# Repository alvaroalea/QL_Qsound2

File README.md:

# Sinclair QL Qsound2+
## Soundcard compatible with QsoundQprint for Sinclair QL

WARNING!!!  Actually there is a problem with this design and is not Fully Compatible with QSound, still need to do more test, music sound at half frecuency, so it's out of tune, and probably effects will be diferents.

(C) 2024 Alvaro Alea Fernandez

License under: CERN Open Hardware Licence Version 2 - Strongly Reciprocal

https://ohwr.org/cern_ohl_s_v2.txt

I upgrade the original desing:

- Using a YM2203, compatible with AY-3-8910 but add a FM sound Chanel
- Add a second way to access the chip, without the PIA (MC6821) to speedup the access.
- Fixed 2Mhz clock, same that Atari ST
- Stereo Output (ABC or ACB selectable by jumpers)

- Remain compatible with Qsound (include a jumper to select internal clock reference as in Qsound)

You can use a 2764 eprom or a W27C512 flash, that is much more cheap and easy to use.

Refer to the original repository for more information about Qsound: https://github.com/alvaroalea/QL_QsoundQprint_clone

## Technical details:
The Card reserve 16Kb of Memory space following Sinclair's P'N'P Way, this mean that is not compatible with 768Kb Trump Card, and that in most of the QL will end on the 0xC0000 - 0xC3FFFF.

The first 8Kb are occuped by the ROM

The next  4Kb are occuped by the MC6821 like in normal QSound

The last 4Kb are used for direct access to the YM2203, it use also A1, so there are two directions:

Write 0xC3000 ->  Write Address Register

Read  0xC3000 -> Read Status

Write 0xC3002 -> Write Register Value

Read  0xC3002 -> Read Register Value

There is no way to know which Clock is selected or Stereo type, this is handmade selections.

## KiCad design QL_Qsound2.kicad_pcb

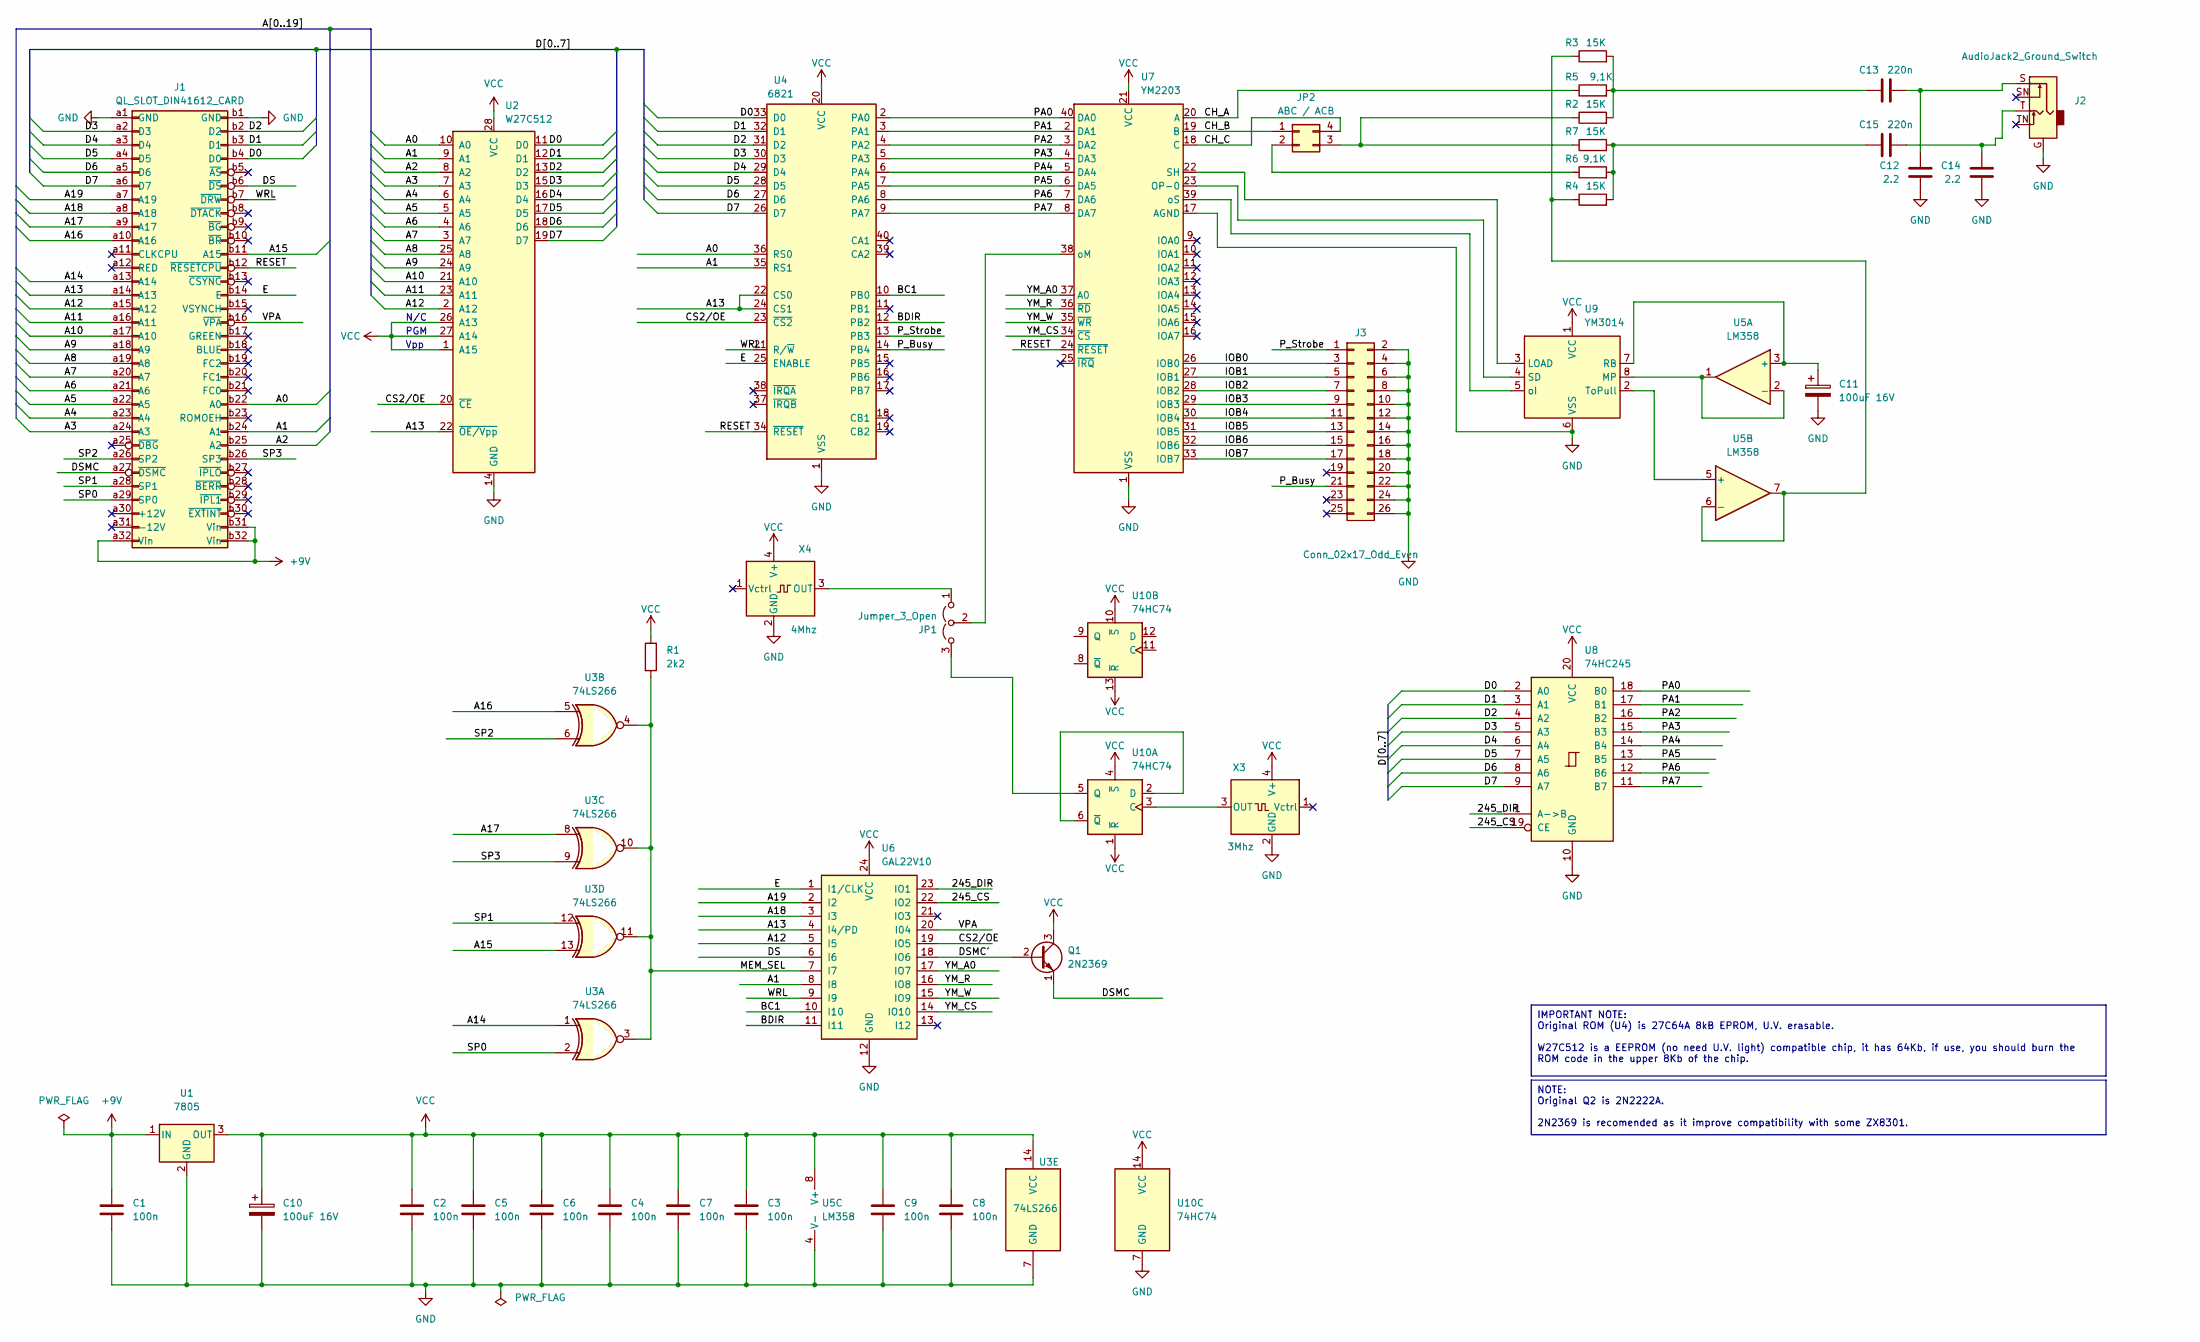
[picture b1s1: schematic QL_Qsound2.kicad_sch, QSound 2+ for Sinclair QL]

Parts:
C1, C2, C3, C4, C5, C6, C7, C8, C9: 100n; C_Disc_D4.3mm_W1.9mm_P5.00mm
C10, C11: 100uF 16V; CP_Radial_D8.0mm_P5.00mm
C12, C14: 2.2; C_Disc_D4.3mm_W1.9mm_P5.00mm
C13, C15: 220n; C_Disc_D4.3mm_W1.9mm_P5.00mm
J1: QL_SLOT_DIN41612_CARD; DIN41612_B_2x32_Female_Horizontal_THT
J2: AudioJack2_Ground_Switch
J3: Conn_02x17_Odd_Even; PinHeader_2x13_P2.54mm_Vertical
JP1: Jumper_3_Open; PinHeader_1x03_P2.54mm_Vertical
JP2: ABC / ACB; PinHeader_2x02_P2.54mm_Vertical
Q1: 2N2369; TO-92_Inline
R1: 2k2; R_Axial_DIN0207_L6.3mm_D2.5mm_P7.62mm_Horizontal
R2, R3, R4, R7: 15K; R_Axial_DIN0207_L6.3mm_D2.5mm_P7.62mm_Horizontal
R5, R6: 9,1K; R_Axial_DIN0207_L6.3mm_D2.5mm_P7.62mm_Horizontal
U1: 7805; TO-220-3_Horizontal_TabDown
U2: W27C512; DIP-28_W15.24mm_LongPads
U3: 74LS266; DIP-14_W7.62mm_LongPads
U4: 6821; DIP-40_W15.24mm_LongPads
U5: LM358; DIP-8_W7.62mm_LongPads
U6: GAL22V10; DIP-24_W7.62mm_LongPads
U7: YM2203; DIP-40_W15.24mm_LongPads
U8: 74HC245; DIP-20_W7.62mm_LongPads
U9: YM3014; DIP-8_W7.62mm_LongPads
U10: 74HC74; DIP-14_W7.62mm_LongPads
X3: 3Mhz; Oscillator_SMD_Abracon_ASV-4Pin_7.0x5.1mm
X4: 4Mhz; Oscillator_SMD_Abracon_ASV-4Pin_7.0x5.1mm

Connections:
+9V: C1.1, J1.a32 (Vin), J1.b31 (Vin), J1.b32 (Vin), U1.1 (IN)
/245_CS: U6.22 (IO2), U8.19 (CE)
/245_DIR: U6.23 (IO1), U8.1 (A->B)
/A0: J1.b22 (A0), U2.10 (A0), U4.36 (RS0)
/A1: J1.b24 (A1), U2.9 (A1), U4.35 (RS1), U6.8 (I8)
/A2: J1.b25 (A2), U2.8 (A2)
/A3: J1.a24 (A3), U2.7 (A3)
/A4: J1.a23 (A4), U2.6 (A4)
/A5: J1.a22 (A5), U2.5 (A5)
/A6: J1.a21 (A6), U2.4 (A6)
/A7: J1.a20 (A7), U2.3 (A7)
/A8: J1.a19 (A8), U2.25 (A8)
/A9: J1.a18 (A9), U2.24 (A9)
/A10: J1.a17 (A10), U2.21 (A10)
/A11: J1.a16 (A11), U2.23 (A11)
/A12: J1.a15 (A12), U2.2 (A12), U6.5 (I5)
/A13: J1.a14 (A13), U2.22 (~OE/Vpp), U4.22 (CS0), U4.24 (CS1), U6.4 (I4/PD)
/A14: J1.a13 (A14), U3.1
/A15: J1.b11 (A15), U3.13
/A16: J1.a10 (A16), U3.5
/A17: J1.a9 (A17), U3.8
/A18: J1.a8 (A18), U6.3 (I3)
/A19: J1.a7 (A19), U6.2 (I2)
/BC1: U4.10 (PB0), U6.10 (I10)
/BDIR: U4.12 (PB2), U6.11 (I11)
/CH_A: R5.1, U7.20 (A)
/CH_B: JP2.1, U7.19 (B)
/CH_C: JP2.4, U7.18 (C)
/CS2/OE: U2.20 (~CE), U4.23 (~CS2), U6.19 (IO5)
/D0: J1.b4 (D0), U2.11 (D0), U4.33 (D0), U8.2 (A0)
/D1: J1.b3 (D1), U2.12 (D1), U4.32 (D1), U8.3 (A1)
/D2: J1.b2 (D2), U2.13 (D2), U4.31 (D2), U8.4 (A2)
/D3: J1.a2 (D3), U2.15 (D3), U4.30 (D3), U8.5 (A3)
/D4: J1.a3 (D4), U2.16 (D4), U4.29 (D4), U8.6 (A4)
/D5: J1.a4 (D5), U2.17 (D5), U4.28 (D5), U8.7 (A5)
/D6: J1.a5 (D6), U2.18 (D6), U4.27 (D6), U8.8 (A6)
/D7: J1.a6 (D7), U2.19 (D7), U4.26 (D7), U8.9 (A7)
/DS: J1.b6 (~DS), U6.6 (I6)
/DSMC: J1.a27 (~DSMC), Q1.1 (E)
/DSMC': Q1.2 (B), U6.18 (IO6)
/E: J1.b14 (E), U4.25 (ENABLE), U6.1 (I1/CLK)
/IOB0: J3.3, U7.26 (IOB0)
/IOB1: J3.5, U7.27 (IOB1)
/IOB2: J3.7, U7.28 (IOB2)
/IOB3: J3.9, U7.29 (IOB3)
/IOB4: J3.11, U7.30 (IOB4)
/IOB5: J3.13, U7.31 (IOB5)
/IOB6: J3.15, U7.32 (IOB6)
/IOB7: J3.17, U7.33 (IOB7)
/MEM_SEL: R1.2, U3.3, U3.4, U3.10, U3.11, U6.7 (I7)
/PA0: U4.2 (PA0), U7.40 (DA0), U8.18 (B0)
/PA1: U4.3 (PA1), U7.2 (DA1), U8.17 (B1)
/PA2: U4.4 (PA2), U7.3 (DA2), U8.16 (B2)
/PA3: U4.5 (PA3), U7.4 (DA3), U8.15 (B3)
/PA4: U4.6 (PA4), U7.5 (DA4), U8.14 (B4)
/PA5: U4.7 (PA5), U7.6 (DA5), U8.13 (B5)
/PA6: U4.8 (PA6), U7.7 (DA6), U8.12 (B6)
/PA7: U4.9 (PA7), U7.8 (DA7), U8.11 (B7)
/P_Busy: J3.21, U4.14 (PB4)
/P_Strobe: J3.1, U4.13 (PB3)
/RESET: J1.b12 (~RESETCPU), U4.34 (~RESET), U7.24 (~RESET)
/SP0: J1.a29 (SP0), U3.2
/SP1: J1.a28 (SP1), U3.12
/SP2: J1.a26 (SP2), U3.6
/SP3: J1.b26 (SP3), U3.9
/VPA: J1.b16 (~VPA), U6.20 (I04)
/WRL: J1.b7 (~DRW), U4.21 (R/~W), U6.9 (I9)
/YM_A0: U6.17 (IO7), U7.37 (A0)
/YM_CS: U6.14 (IO10), U7.34 (~CS)
/YM_R: U6.16 (IO8), U7.36 (~RD)
/YM_W: U6.15 (IO9), U7.35 (~WR)
GND: C1.2, C2.2, C3.2, C4.2, C5.2, C6.2, C7.2, C8.2, C9.2, C10.2, C11.2, C12.2, C14.2, J1.a1 (GND), J1.b1 (GND), J2.G, J3.2, J3.4, J3.6, J3.8, J3.10, J3.12, J3.14, J3.16, J3.18, J3.20, J3.22, J3.24, J3.26, U1.2 (GND), U2.14 (GND), U3.7 (GND), U4.1 (VSS), U5.4 (V-), U6.12 (GND), U7.1 (VSS), U7.17 (AGND), U8.10 (GND), U9.6 (VSS), U10.7 (GND), X3.2 (GND), X4.2 (GND)
unnamed: C12.1, C13.2, J2.S
unnamed: C13.1, R2.2, R3.2, R5.2
unnamed: C14.1, C15.2, J2.T
unnamed: C15.1, R4.2, R6.2, R7.2
unnamed: JP1.1 (A), X4.3 (OUT)
unnamed: JP1.3 (B), U10.5 (Q)
unnamed: JP1.2 (C), U7.38 (oM)
unnamed: JP2.2, R6.1
unnamed: JP2.3, R2.1, R7.1
unnamed: C11.1, U5.3 (+), U9.7 (RB)
unnamed: U5.1, U5.2 (-), U9.8 (MP)
unnamed: U5.5 (+), U9.2 (ToPull)
unnamed: R3.1, R4.1, U5.6 (-), U5.7
unnamed: U7.23 (OP-0), U9.4 (SD)
unnamed: U7.22 (SH), U9.3 (LOAD)
unnamed: U7.39 (oS), U9.5 (oI)
unnamed: U10.3 (C), X3.3 (OUT)
unnamed: U10.2 (D), U10.6 (~Q)
VCC: C2.1, C3.1, C4.1, C5.1, C6.1, C7.1, C8.1, C9.1, C10.1, Q1.3 (C), R1.1, U1.3 (OUT), U2.1 (A15), U2.26 (A13), U2.27 (A14), U2.28 (VCC), U3.14 (VCC), U4.20 (VCC), U5.8 (V+), U6.24 (VCC), U7.21 (VCC), U8.20 (VCC), U9.1 (VCC), U10.1 (~R), U10.4 (~S), U10.10 (~S), U10.13 (~R), U10.14 (VCC), X3.4 (V+), X4.4 (V+)

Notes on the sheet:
NOTE: Original Q2 is 2N2222A. 2N2369 is recomended as it improve compatibility with some ZX8301.
IMPORTANT NOTE: Original ROM (U4) is 27C64A 8kB EPROM, U.V. erasable. W27C512 is a EEPROM (no need U.V. light) compatible chip, it has 64Kb, if use, you should burn the ROM code in the upper 8Kb of the chip.
Vpp
N/C
PGM

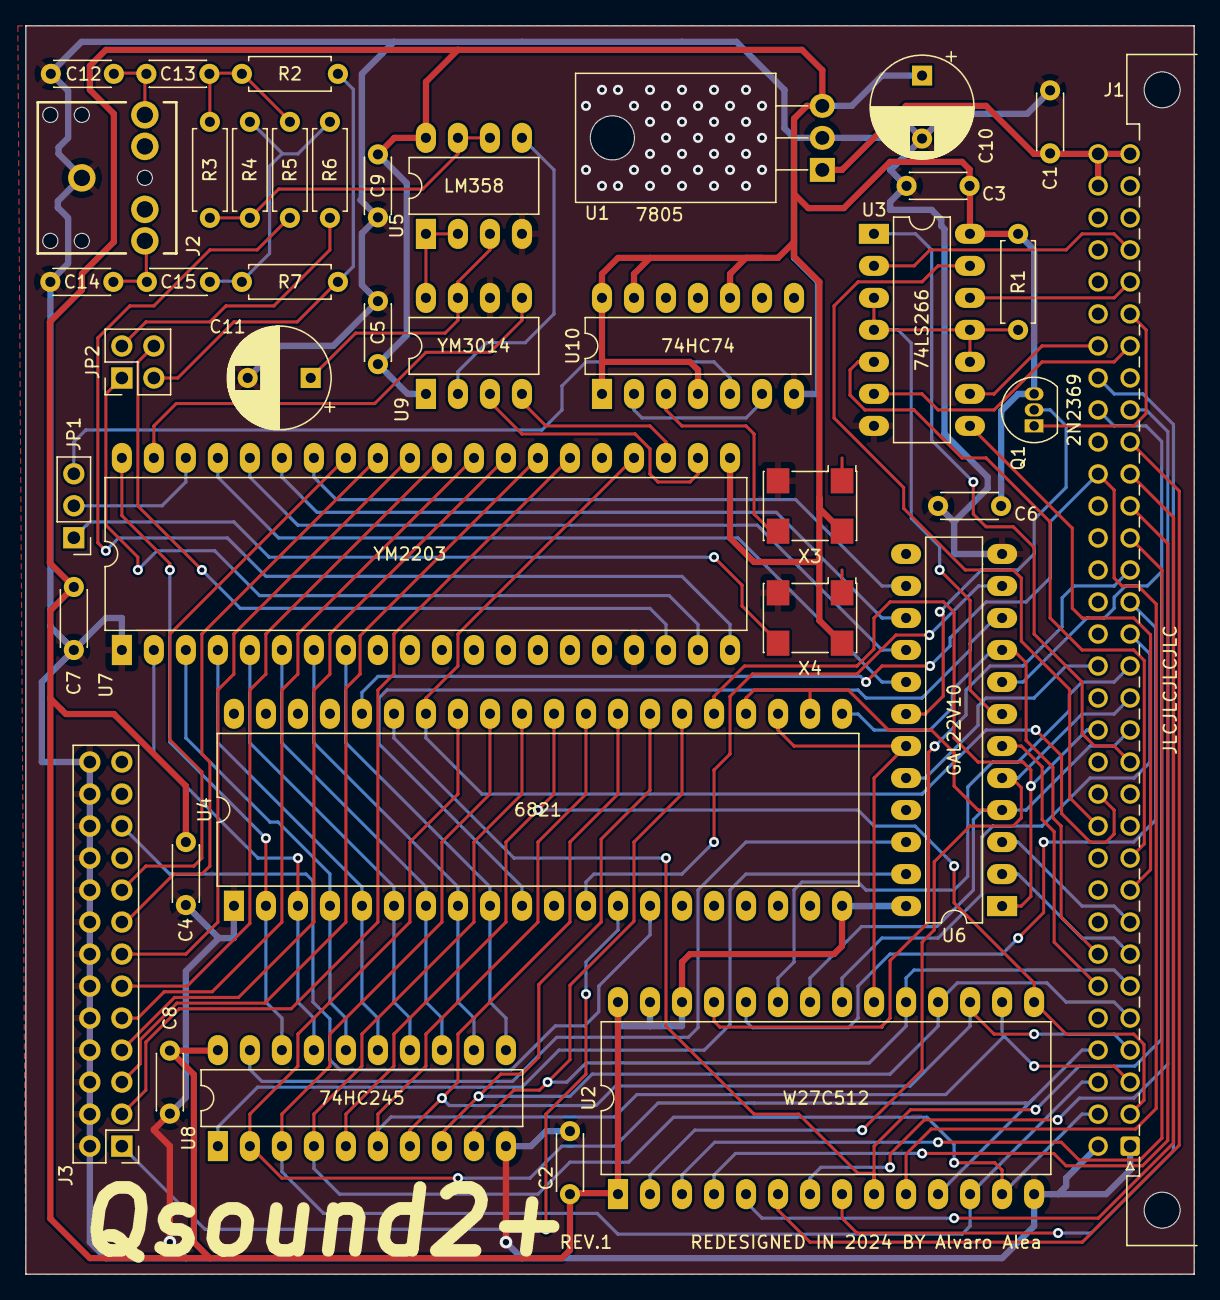
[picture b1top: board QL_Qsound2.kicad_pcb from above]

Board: 2 copper layers, 92.7 x 99.1 mm, 40 parts (0 on the bottom side), 91 nets.

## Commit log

2024-11-10 Initial
2024-11-11 ADD NOTE
2024-11-13 new clock oscilators

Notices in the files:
QL_Qsound2.kicad_pcb:
Licensed under Cern OHL-S
